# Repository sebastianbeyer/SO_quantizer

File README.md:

Kosmo format quantizer based largely on the [kassutronics quantizer](https://store.kassutronics.net/eurorack-diy-c-1/quantizer-p-1). 
I went for a different interface though, where you select the scale via potentiometer and with the second potentiometer (and cv input) you can bias the incoming voltages and therefore 'transpose in scale'. 
It still lacks a few scales.

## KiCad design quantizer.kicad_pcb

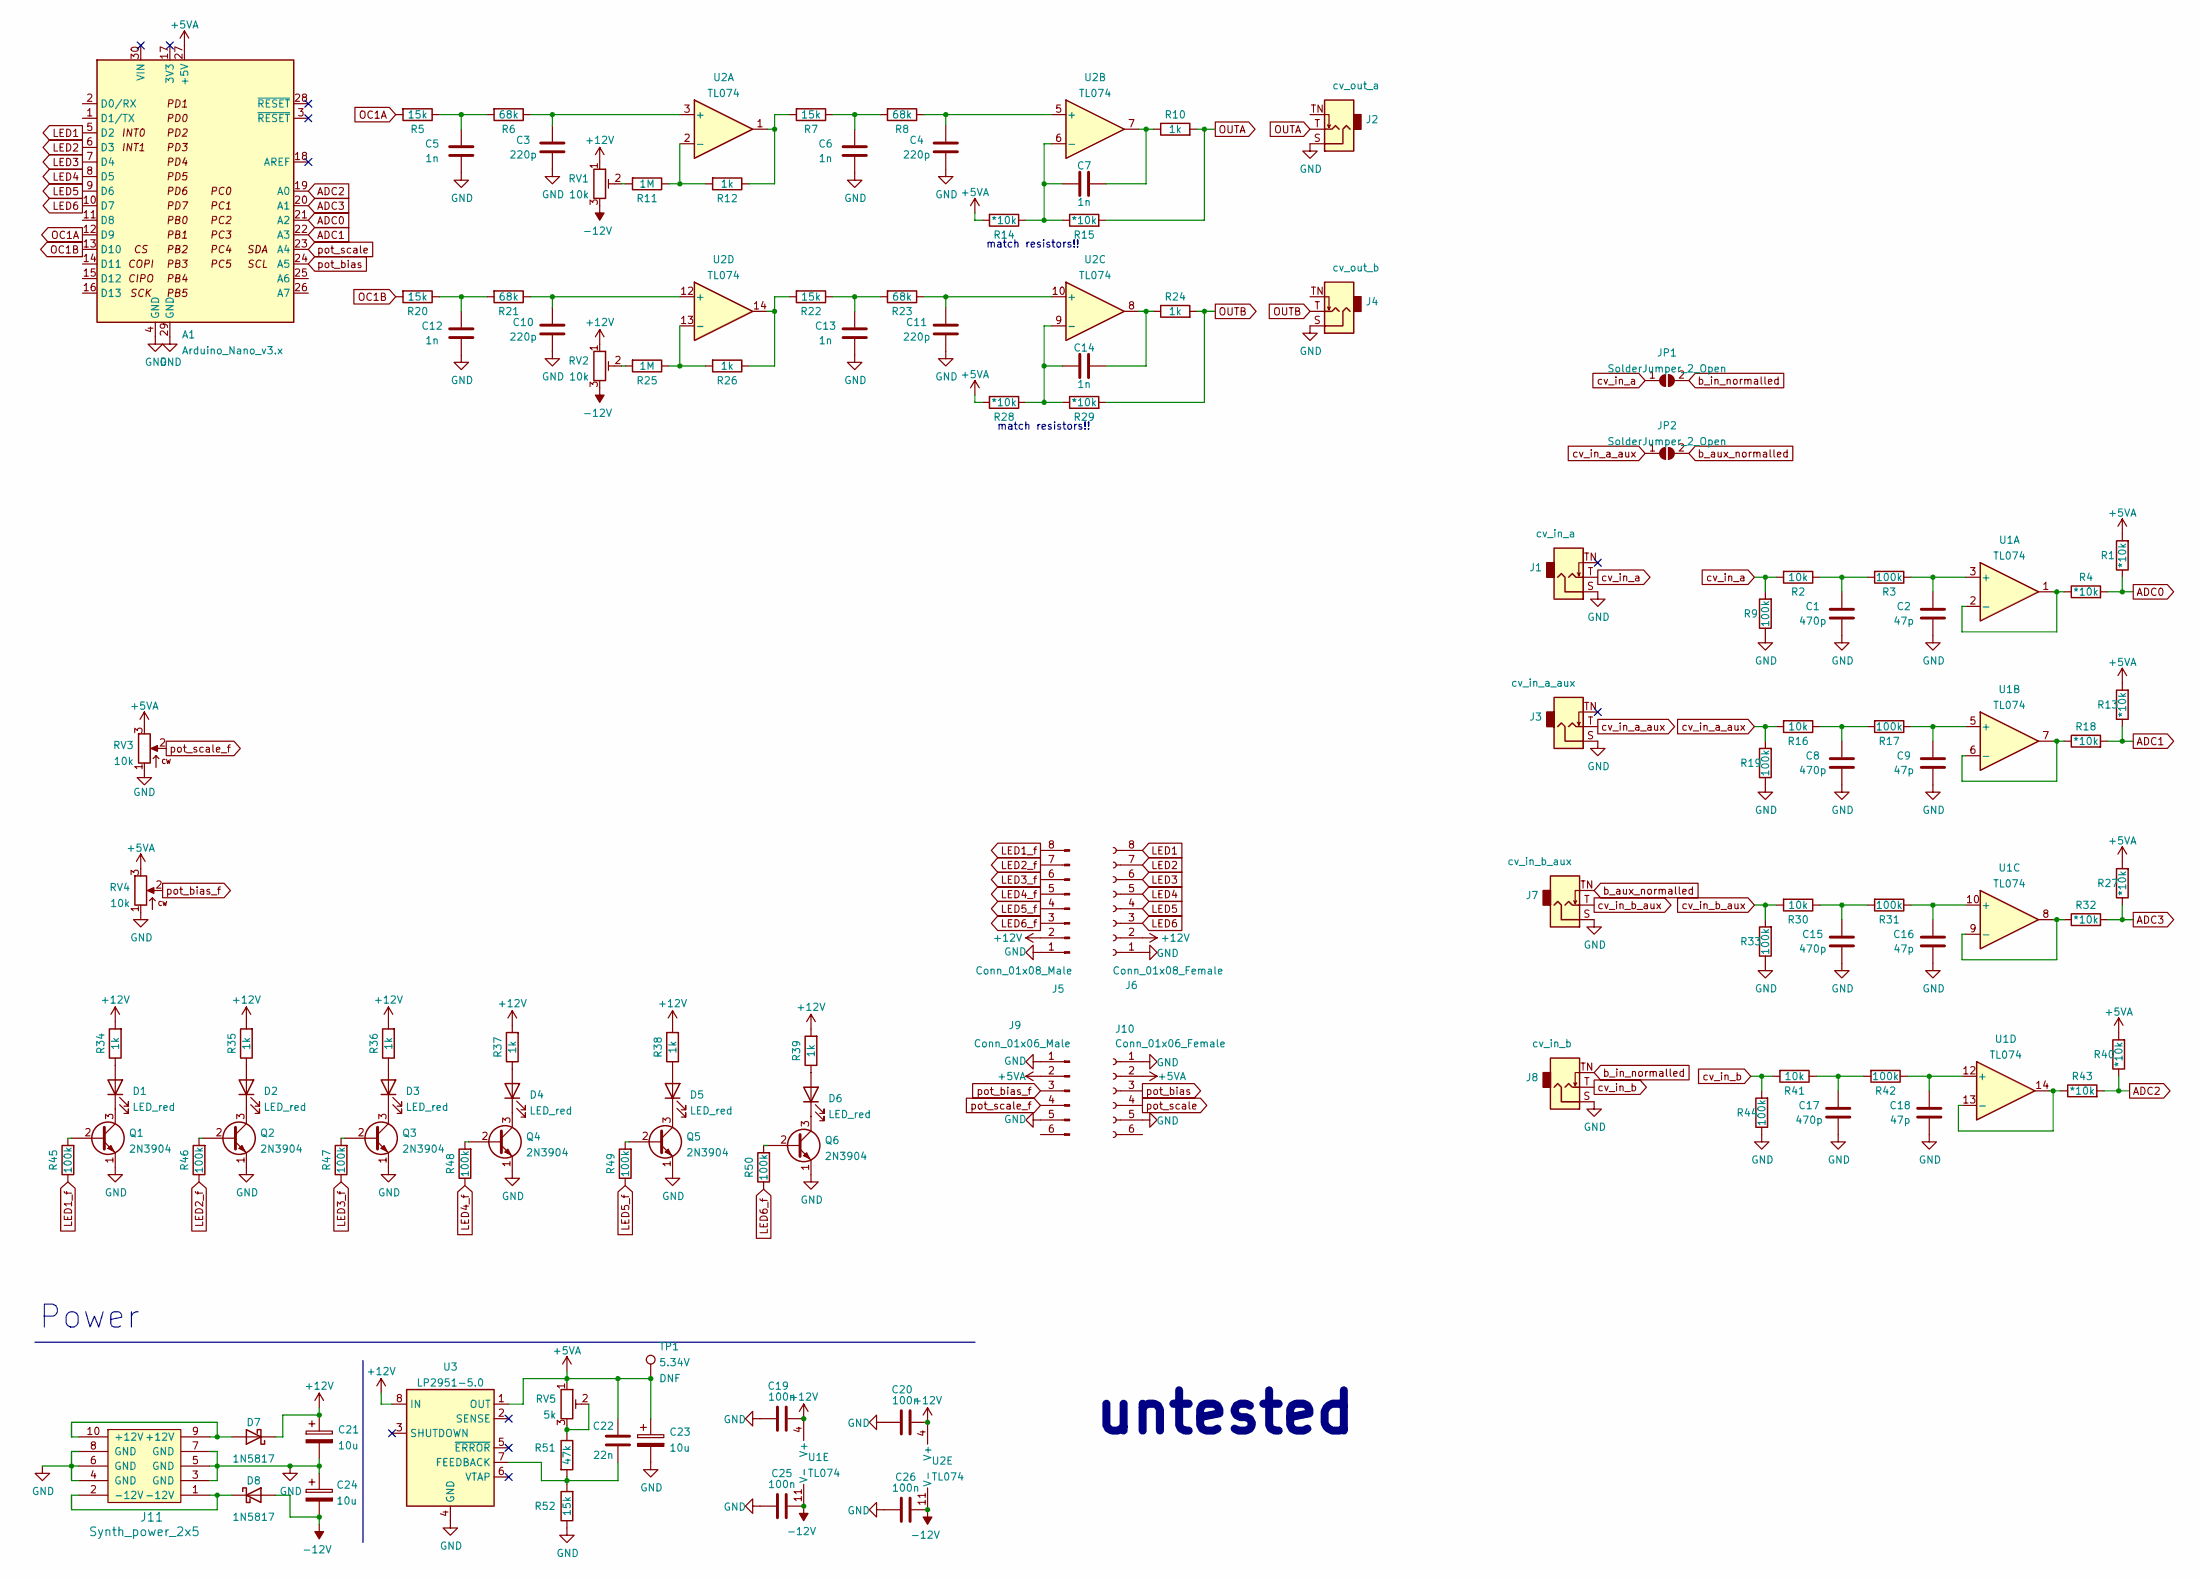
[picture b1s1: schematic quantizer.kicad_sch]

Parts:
A1: Arduino_Nano_v3.x; Arduino_Nano
C1, C8, C15, C17: 470p; C_Disc_D3.0mm_W1.6mm_P2.50mm
C2, C9, C16, C18: 47p; C_Disc_D3.0mm_W1.6mm_P2.50mm
C3, C4, C10, C11: 220p; C_Disc_D3.0mm_W1.6mm_P2.50mm
C5, C6, C7, C12, C13, C14: 1n; C_Disc_D3.0mm_W1.6mm_P2.50mm
C19, C20, C25, C26: 100n; C_Disc_D3.0mm_W1.6mm_P2.50mm
C21, C23, C24: 10u; CP_Radial_horizontalflat_D5mm_P2.50mm_H10mm_south
C22: 22n; C_Rect_L7.2mm_W2.5mm_P5.00mm_FKS2_FKP2_MKS2_MKP2
D1, D2, D3, D4, D5, D6: LED_red; LED_D3.0mm_FlatTop
D7, D8: 1N5817; D_DO-41_SOD81_P10.16mm_Horizontal
J1: cv_in_a; Jack_6.35mm_PJ_629HAN
J2: cv_out_a; Jack_6.35mm_PJ_629HAN
J3: cv_in_a_aux; Jack_6.35mm_PJ_629HAN
J4: cv_out_b; Jack_6.35mm_PJ_629HAN
J5: Conn_01x08_Male; PinHeader_1x08_P2.54mm_Vertical
J6: Conn_01x08_Female; PinSocket_1x08_P2.54mm_Vertical
J7: cv_in_b_aux; Jack_6.35mm_PJ_629HAN
J8: cv_in_b; Jack_6.35mm_PJ_629HAN
J9: Conn_01x06_Male; PinHeader_1x06_P2.54mm_Vertical
J10: Conn_01x06_Female; PinSocket_1x06_P2.54mm_Vertical
J11: Synth_power_2x5; Power_Header
JP1, JP2: SolderJumper_2_Open; SolderJumper-2_P1.3mm_Open_RoundedPad1.0x1.5mm
Q1, Q2, Q3, Q4, Q5, Q6: 2N3904; TO-92_Inline_Wide
R1, R4, R13, R14, R15, R18, R27, R28, R29, R32, R40, R43: *10k; R_Axial_DIN0207_L6.3mm_D2.5mm_P2.54mm_Vertical
R2, R16, R30, R41: 10k; R_Axial_DIN0207_L6.3mm_D2.5mm_P2.54mm_Vertical
R3, R9, R17, R19, R31, R33, R42, R44, R45, R46, R47, R48, R49, R50: 100k; R_Axial_DIN0207_L6.3mm_D2.5mm_P2.54mm_Vertical
R5, R7, R20, R22, R52: 15k; R_Axial_DIN0207_L6.3mm_D2.5mm_P2.54mm_Vertical
R6, R8, R21, R23: 68k; R_Axial_DIN0207_L6.3mm_D2.5mm_P2.54mm_Vertical
R10, R12, R24, R26, R34, R35, R36, R37, R38, R39: 1k; R_Axial_DIN0207_L6.3mm_D2.5mm_P2.54mm_Vertical
R11, R25: 1M; R_Axial_DIN0207_L6.3mm_D2.5mm_P2.54mm_Vertical
R51: 47k; R_Axial_DIN0207_L6.3mm_D2.5mm_P2.54mm_Vertical
RV1, RV2: 10k; Potentiometer_Bourns_3296Z_Horizontal
RV3, RV4: 10k; Potentiometer_Alpha_RD901F-40-00D_Single_Vertical_centered
RV5: 5k; Potentiometer_Bourns_3296Z_Horizontal
TP1: 5.34V; TestPoint_THTPad_D1.5mm_Drill0.7mm
U1, U2: TL074; DIP-14_W7.62mm_Socket_LongPads
U3: LP2951-5.0; DIP-8_W7.62mm_Socket_LongPads

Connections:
+5VA: A1.27 (+5V), C22.2, C23.1, J9.2, J10.2, R1.2, R13.2, R14.2, R27.2, R28.2, R40.2, RV3.3, RV4.3, RV5.1, TP1.1, U3.1 (OUT)
+12V: C19.2, C20.2, C21.1, D7.1 (K), J5.2, J6.2, R34.2, R35.2, R36.2, R37.2, R38.2, R39.2, RV1.1, RV2.1, U1.4 (V+), U2.4 (V+), U3.8 (IN)
-12V: C24.2, C25.2, C26.2, D8.2 (A), RV1.3, RV2.3, U1.11 (V-), U2.11 (V-)
ADC0: A1.21 (A2), R1.1, R4.2
ADC1: A1.22 (A3), R13.1, R18.2
ADC2: A1.19 (A0), R40.1, R43.2
ADC3: A1.20 (A1), R27.1, R32.2
GND: A1.4 (GND), A1.29 (GND), C1.1, C2.1, C3.1, C4.1, C5.1, C6.1, C8.1, C9.1, C10.1, C11.1, C12.1, C13.1, C15.1, C16.1, C17.1, C18.1, C19.1, C20.1, C21.2, C23.2, C24.1, C25.1, C26.1, J1.S, J2.S, J3.S, J4.S, J5.1, J6.1, J7.S, J8.S, J9.1, J9.5, J10.1, J10.5, J11.3 (GND), J11.4 (GND), J11.5 (GND), J11.6 (GND), J11.7 (GND), J11.8 (GND), Q1.1 (E), Q2.1 (E), Q3.1 (E), Q4.1 (E), Q5.1 (E), Q6.1 (E), R9.1, R19.1, R33.1, R44.1, R52.1, RV3.1, RV4.1, U3.4 (GND); also elsewhere on the board
LED1: A1.5 (D2), J6.8
LED1_f: J5.8, R45.1
LED2: A1.6 (D3), J6.7
LED2_f: J5.7, R46.1
LED3: A1.7 (D4), J6.6
LED3_f: J5.6, R47.1
LED4: A1.8 (D5), J6.5
LED4_f: J5.5, R48.1
LED5: A1.9 (D6), J6.4
LED5_f: J5.4, R49.1
LED6: A1.10 (D7), J6.3
LED6_f: J5.3, R50.1
unnamed: C1.2, R2.1, R3.2
unnamed: C2.2, R3.1, U1.3 (+)
unnamed: C3.2, R6.1, U2.3 (+)
unnamed: C4.2, R8.1, U2.5 (+)
unnamed: C5.2, R5.1, R6.2
unnamed: C6.2, R7.1, R8.2
unnamed: C7.1, R10.1, U2.7
unnamed: C7.2, R14.1, R15.1, U2.6 (-)
unnamed: C8.2, R16.1, R17.2
unnamed: C9.2, R17.1, U1.5 (+)
unnamed: C10.2, R21.1, U2.12 (+)
unnamed: C11.2, R23.1, U2.10 (+)
unnamed: C12.2, R20.1, R21.2
unnamed: C13.2, R22.1, R23.2
unnamed: C14.1, R24.1, U2.8
unnamed: C14.2, R28.1, R29.1, U2.9 (-)
unnamed: C15.2, R30.1, R31.2
unnamed: C16.2, R31.1, U1.10 (+)
unnamed: C17.2, R41.1, R42.2
unnamed: C18.2, R42.1, U1.12 (+)
unnamed: C22.1, R51.2, R52.2, U3.7 (FEEDBACK)
unnamed: D1.1 (K), Q1.3 (C)
unnamed: D1.2 (A), R34.1
unnamed: D2.1 (K), Q2.3 (C)
unnamed: D2.2 (A), R35.1
unnamed: D3.1 (K), Q3.3 (C)
unnamed: D3.2 (A), R36.1
unnamed: D4.1 (K), Q4.3 (C)
unnamed: D4.2 (A), R37.1
unnamed: D5.1 (K), Q5.3 (C)
unnamed: D5.2 (A), R38.1
unnamed: D6.1 (K), Q6.3 (C)
unnamed: D6.2 (A), R39.1
unnamed: D7.2 (A), J11.9 (+12V), J11.10 (+12V)
unnamed: D8.1 (K), J11.1 (-12V), J11.2 (-12V)
unnamed: Q1.2 (B), R45.2
unnamed: Q2.2 (B), R46.2
unnamed: Q3.2 (B), R47.2
unnamed: Q4.2 (B), R48.2
unnamed: Q5.2 (B), R49.2
unnamed: Q6.2 (B), R50.2
unnamed: R4.1, U1.1, U1.2 (-)
unnamed: R11.1, R12.2, U2.2 (-)
unnamed: R11.2, RV1.2
unnamed: R7.2, R12.1, U2.1
unnamed: R18.1, U1.6 (-), U1.7
unnamed: R22.2, R26.1, U2.14
unnamed: R25.1, R26.2, U2.13 (-)
unnamed: R25.2, RV2.2
unnamed: R32.1, U1.8, U1.9 (-)
unnamed: R43.1, U1.13 (-), U1.14
unnamed: R51.1, RV5.2, RV5.3
OC1A: A1.12 (D9), R5.2
OC1B: A1.13 (D10), R20.2
OUTA: J2.T, R10.2, R15.2
OUTB: J4.T, R24.2, R29.2
b_aux_normalled: J7.TN, JP2.2 (B)
b_in_normalled: J8.TN, JP1.2 (B)
cv_in_a: J1.T, JP1.1 (A), R2.2, R9.2
cv_in_a_aux: J3.T, JP2.1 (A), R16.2, R19.2
cv_in_b: J8.T, R41.2, R44.2
cv_in_b_aux: J7.T, R30.2, R33.2
pot_bias: A1.24 (A5), J10.3
pot_bias_f: J9.3, RV4.2
pot_scale: A1.23 (A4), J10.4
pot_scale_f: J9.4, RV3.2

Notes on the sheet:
untested
match resistors!!
Power

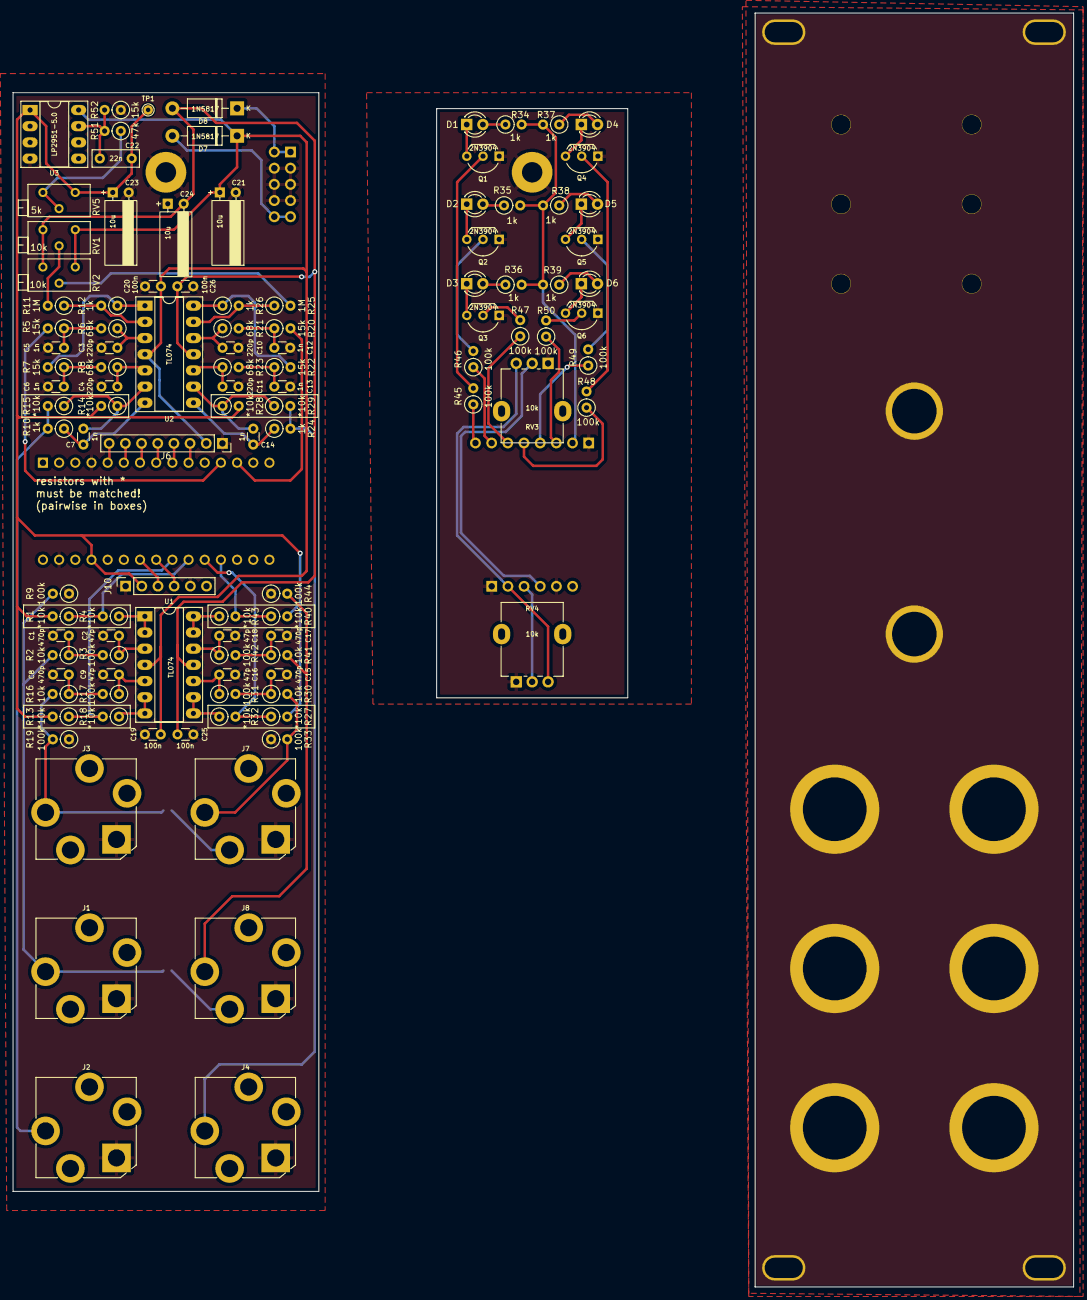
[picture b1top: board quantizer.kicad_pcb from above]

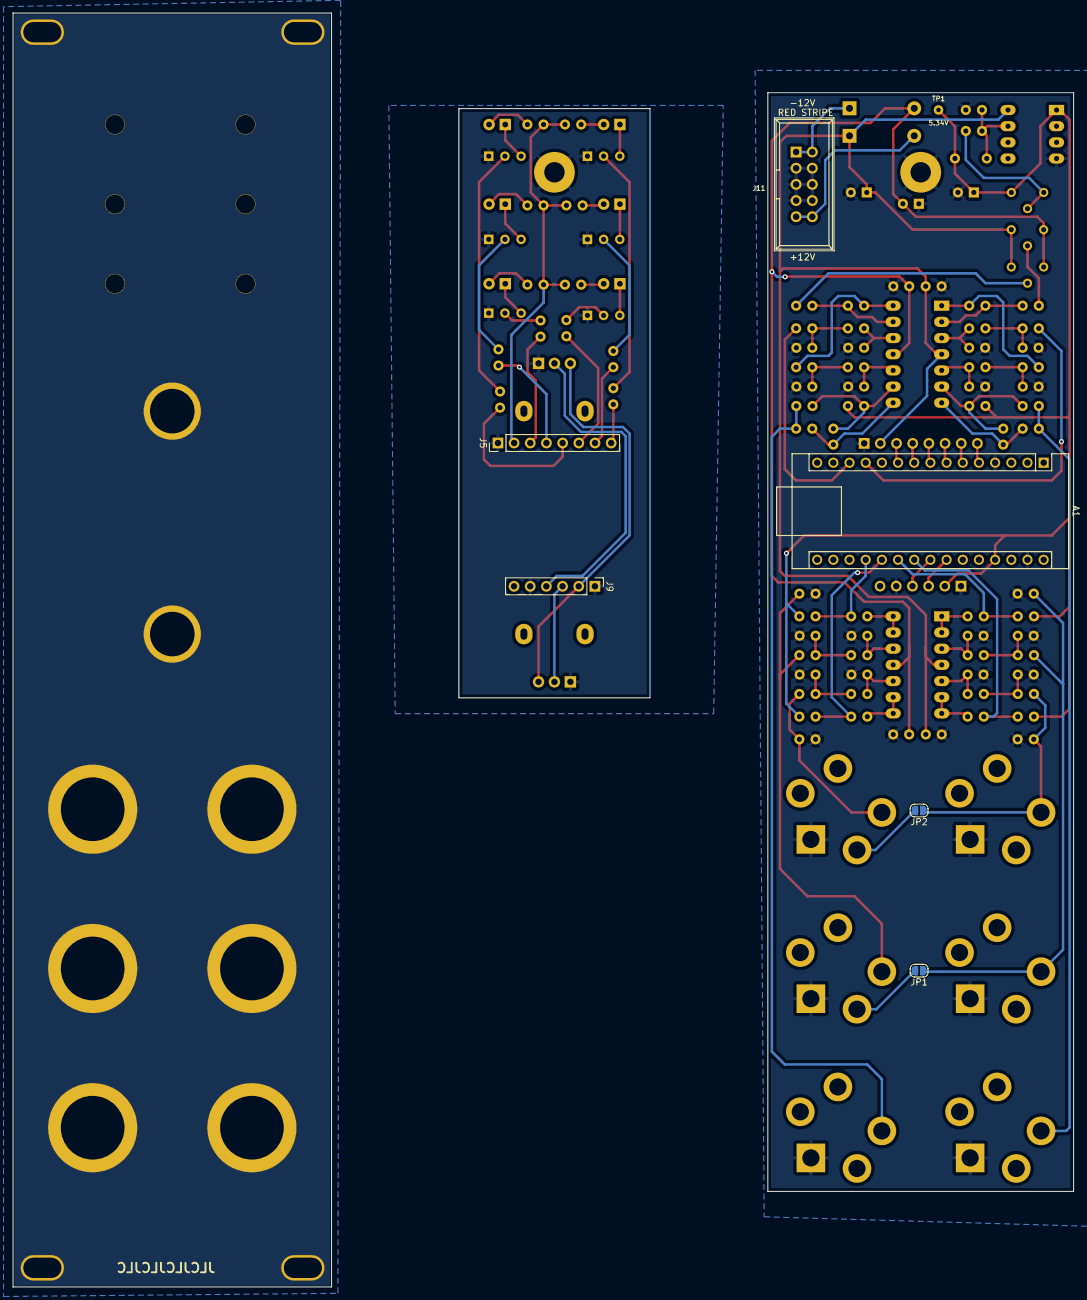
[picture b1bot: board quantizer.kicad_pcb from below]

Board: 2 copper layers, 166.5 x 200.0 mm, 117 parts (6 on the bottom side), 86 nets.

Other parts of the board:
 : MountingHole_3.2mm_M3_Pad
 #2: MountingHole_3.2mm_M3_Pad

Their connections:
GND: .1, #2.1; also elsewhere on the board

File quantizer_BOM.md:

# quantizer.kicad_sch BOM

Tue 03 Jan 2023 10:16:02 CET

Generated from schematic by Eeschema 6.0.8-f2edbf62ab~116~ubuntu22.04.1

**Component Count:** 114

| Refs | Qty | Component | Description | Vendor | SKU |
| ----- | --- | ---- | ----------- | ---- | ---- |
| A1 | 1 | Arduino_Nano_v3.x | Arduino Nano v3.x |  |  |
| C1, C8, C15, C17 | 4 | 470p | Unpolarized capacitor |  |  |
| C2, C9, C16, C18 | 4 | 47p | Unpolarized capacitor |  |  |
| C3, C4, C10, C11 | 4 | 220p | Unpolarized capacitor |  |  |
| C5, C6, C7, C12, C13, C14 | 6 | 1n | Unpolarized capacitor |  |  |
| C19, C20, C25, C26 | 4 | 100n | Unpolarized capacitor |  |  |
| C21, C23, C24 | 3 | 10u | Polarized capacitor | Tayda |  |
| C22 | 1 | 22n | Unpolarized capacitor |  |  |
| D1, D2, D3, D4, D5, D6 | 6 | LED_red | Light emitting diode | Tayda | A-1554 |
| D7, D8 | 2 | 1N5817 | Schottky Barrier Rectifier Diode, DO-41 | Tayda | A-159 |
| J1 | 1 | cv_in_a | Audio Jack, 2 Poles (Mono / TS), Switched T Pole (Normalling) | Tayda | A-1121 |
| J2 | 1 | cv_out_a | Audio Jack, 2 Poles (Mono / TS), Switched T Pole (Normalling) | Tayda | A-1121 |
| J3 | 1 | cv_in_a_aux | Audio Jack, 2 Poles (Mono / TS), Switched T Pole (Normalling) | Tayda | A-1121 |
| J4 | 1 | cv_out_b | Audio Jack, 2 Poles (Mono / TS), Switched T Pole (Normalling) | Tayda | A-1121 |
| J5 | 1 | Conn_01x08_Male | Generic connector, single row, 01x08, script generated (kicad-library-utils/schlib/autogen/connector/) |  |  |
| J6 | 1 | Conn_01x08_Female | Generic connector, single row, 01x08, script generated (kicad-library-utils/schlib/autogen/connector/) |  |  |
| J7 | 1 | cv_in_b_aux | Audio Jack, 2 Poles (Mono / TS), Switched T Pole (Normalling) | Tayda | A-1121 |
| J8 | 1 | cv_in_b | Audio Jack, 2 Poles (Mono / TS), Switched T Pole (Normalling) | Tayda | A-1121 |
| J9 | 1 | Conn_01x06_Male | Generic connector, single row, 01x06, script generated (kicad-library-utils/schlib/autogen/connector/) |  |  |
| J10 | 1 | Conn_01x06_Female | Generic connector, single row, 01x06, script generated (kicad-library-utils/schlib/autogen/connector/) |  |  |
| J11 | 1 | Synth_power_2x5 | Pin header 2.54 mm 2x5 | Tayda | A-2939 |
| JP1, JP2 | 2 | SolderJumper_2_Open | Solder Jumper, 2-pole, open |  |  |
| Q1, Q2, Q3, Q4, Q5, Q6 | 6 | 2N3904 | Small Signal NPN Transistor, TO-92 | Tayda | A-111 |
| R1, R4, R13, R14, R15, R18, R27, R28, R29, R32, R40, R43 | 12 | *10k | Resistor | Tayda |  |
| R2, R16, R30, R41 | 4 | 10k | Resistor | Tayda |  |
| R3, R9, R17, R19, R31, R33, R42, R44, R45, R46, R47, R48, R49, R50 | 14 | 100k | Resistor | Tayda |  |
| R5, R7, R20, R22, R52 | 5 | 15k | Resistor | Tayda |  |
| R6, R8, R21, R23 | 4 | 68k | Resistor | Tayda |  |
| R10, R12, R24, R26, R34, R35, R36, R37, R38, R39 | 10 | 1k | Resistor | Tayda |  |
| R11, R25 | 2 | 1M | Resistor | Tayda |  |
| R51 | 1 | 47k | Resistor | Tayda |  |
| RV1, RV2 | 2 | 10k | Trim-potentiometer | Tayda |  |
| RV3, RV4 | 2 | 10k | Potentiometer | Tayda |  |
| RV5 | 1 | 5k | Trim-potentiometer | Tayda |  |
| U1, U2 | 2 | TL074 | Quad operational amplifier, DIP-14 | Tayda | A-1138 |
| U3 | 1 | LP2951-5.0 | Micropower Voltage Regulators with Shutdown, 100mA, Fixed Output 5.0V, LDO, DIP-8 |  |  |

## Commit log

2023-01-03 initial
2023-05-04 add initial firmware
2023-05-04 add readme
